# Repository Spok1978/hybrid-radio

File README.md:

# IP-Radio — приёмник УКВ/FM + интернет-радио

Проект приёмника с двумя режимами работы:

1. **Эфир** — УКВ OIRT (65,8–74 МГц) и FM CCIR (87,5–108 МГц): автопоиск,
   частота и название станции на экране, ручная настройка, пресеты.
2. **Интернет-радио** — подключение к Wi-Fi, поиск станций, воспроизведение,
   свой список станций.

Один цветной экран на оба режима, экранное меню + кнопки и энкодеры, один
громкоговоритель, переключение режимов программное — пресетом, кнопкой MODE
или через меню ([22](docs/22-mode-switching.md)).

## Статус

**Прошивка написана и работает на плате.** Интернет-радио играет со звуком,
экран и касание живые, Wi-Fi подключается, станции ищутся в каталоге
radio-browser и сохраняются на карту. Идёт отладка на Waveshare
ESP32-P4-WIFI6-Touch-LCD-5.

Оговорки, важные для понимания статуса:

* Звук временно идёт в **штатный кодек платы ES8311**, а не в целевой
  PCM5102A с усилителем TPA3118: своя обвязка ещё не подключена.
  Переключается ключом `IPRADIO_USE_BOARD_CODEC` в `firmware/main/board_pins.h`.
* **Внешней обвязки нет вовсе** — ни тюнера RDA5807M, ни кнопок,
  ни энкодеров. Поэтому всё управление продублировано касанием.
  Эфирный режим в коде есть, но проверить его нечем.
* УКВ OIRT отключён решением заказчика, `IPRADIO_ENABLE_OIRT 0`.

Что именно сделано и что осталось — [firmware/README.md](firmware/README.md).

**2026-08-26 — основная сборка перенесена на ESP32-P4** (плата Waveshare
ESP32-P4-WIFI6-Touch-LCD-5), список станций хранится в штатном формате
её прошивки. Разбор переноса, что переезжает без изменений и что открылось
заново — [docs/24-main-build-p4.md](docs/24-main-build-p4.md). Таблица решений
и схема ниже — для сборки на ESP32-P4. Ранняя ревизия на Raspberry Pi
отменена; её документы помечены в шапке «НЕАКТУАЛЬНО» и для сборки не
применяются (в таблице ниже — с пометкой).

Открытые вопросы — в [docs/06-open-questions.md](docs/06-open-questions.md),
сейчас их четыре: Q7, Q8, Q10 и Q14.
Q13 закрыт 2026-08-26 — [25](docs/25-station-storage.md), §9.

## Документы

| Файл | О чём |
|---|---|
| [00-requirements.md](docs/00-requirements.md) | Требования (R1…R2.6), что именно должен уметь приёмник |
| [01-station-directories.md](docs/01-station-directories.md) | **Как устроено интернет-радио и откуда брать список станций.** Разбор Radio Browser, SHOUTcast, Xiph, TuneIn, vTuner/Airable + сравнение |
| [02-fm-frontend.md](docs/02-fm-frontend.md) | Эфирный тракт: RDA5807M / Si4735 / RTL-SDR, диапазоны, RDS, что не так с УКВ OIRT |
| [03-controller-platform.md](docs/03-controller-platform.md) | *Неактуально (ревизия на Pi).* Нужен ли контроллер и какой |
| [04-audio-path.md](docs/04-audio-path.md) | ЦАП, усилитель, динамик, как свести два источника в один тракт |
| [05-display-and-ui.md](docs/05-display-and-ui.md) | *Неактуально (ревизия на Pi).* Экран, кнопки, энкодер, структура экранного меню |
| [06-open-questions.md](docs/06-open-questions.md) | **Вопросы Q1…Q10: что решено, что открыто** |
| [07-bom-draft.md](docs/07-bom-draft.md) | *Неактуально (ревизия на Pi).* Черновой состав комплекта |
| [08-cost-and-board-choice.md](docs/08-cost-and-board-choice.md) | *Неактуально (ревизия на Pi).* Стоимость и выбор платы |
| [09-power-supply.md](docs/09-power-supply.md) | *Неактуально (ревизия на Pi).* Питание; входная защита и 3,3 В тюнера перенесены в [33](docs/33-carrier-board.md) |
| [10-shutdown-and-data-safety.md](docs/10-shutdown-and-data-safety.md) | *Неактуально (ревизия на Pi, Linux).* Выключение питания и сохранность данных |
| [11-shopping-list.md](docs/11-shopping-list.md) | *Неактуально (ревизия на Pi).* Список покупок; актуальный перечень деталей — [35](docs/35-carrier-boards-parts.md) |
| [12-audit-response.md](docs/12-audit-response.md) | *Неактуально (ревизия на Pi).* Разбор внешнего аудита |
| [13-gpio-map.md](docs/13-gpio-map.md) | *Неактуально (ревизия на Pi).* Карта GPIO; актуальные выводы — [33](docs/33-carrier-board.md) §2 |
| [14-software-stack.md](docs/14-software-stack.md) | *Неактуально (ревизия на Pi, Linux).* Программный стек; актуальное — [26](docs/26-firmware-spec.md) |
| [15-wiring-breadboard.md](docs/15-wiring-breadboard.md) | *Неактуально (ревизия на Pi).* Схема соединений для макета |
| [16-connection-list.md](docs/16-connection-list.md) | *Неактуально (ревизия на Pi).* Перечень соединений «откуда → куда» |
| [17-audit-response-wiring.md](docs/17-audit-response-wiring.md) | *Неактуально (ревизия на Pi).* Ответ на три внешних разбора схемы |
| [18-similar-projects.md](docs/18-similar-projects.md) | Разбор двух похожих гибридных приёмников: что забрали, что отклонили |
| [35-carrier-boards-parts.md](docs/35-carrier-boards-parts.md) | **Доп. платы: состав и перечень деталей** (91 деталь, три платы) |
| [33-carrier-board.md](docs/33-carrier-board.md) | **Доп. платы к P4**: схема, распиновка гребёнки J3, модули, разводка плат |
| [30-pin-assignment.md](docs/30-pin-assignment.md) | **Раскладка выводов**: две готовые конфигурации до конкретного GPIO, с расширителем портов и без |
| [29-yaml-review.md](docs/29-yaml-review.md) | **Разбор стороннего описания железа**: что подтвердилось по схеме, что оказалось неверным, и почему свободных выводов восемнадцать, а не двадцать один |
| [28-screen-mockups.md](docs/28-screen-mockups.md) | **Образцы экранов**: восемь состояний интерфейса в кадре 1280x720, принятые как рабочий вариант |
| [27-reference-sheet.md](docs/27-reference-sheet.md) | **Лист для сверки**: что берём готового (ESP-ADF, esp_lcd DSI, PPA, esp-hosted), что читаем как референс, и список известных граблей |
| [26-firmware-spec.md](docs/26-firmware-spec.md) | **ТЗ на прошивку** для внешнего исполнителя: черновик заказчика, дополненный данными проекта и исправленный по принятым решениям |
| [25-station-storage.md](docs/25-station-storage.md) | **Хранение станций (Q13, решено)**: почему формат прошивки не расширяется, и почему мастером стал наш файл, а `/stations.json` — проекцией |
| [24-main-build-p4.md](docs/24-main-build-p4.md) | **Перенос основной сборки на ESP32-P4**: что стало основным, формат `/stations.json`, что открылось заново |
| [23-volume-control.md](docs/23-volume-control.md) | **Громкость**: энкодер 2 и mute, одно логическое значение на два тракта, потолок в 16 ступеней у эфира |
| [22-mode-switching.md](docs/22-mode-switching.md) | **Переключение режимов**: почему тумблер отменён, кнопка MODE, единый банк пресетов |
| [21-board-search-criteria.md](docs/21-board-search-criteria.md) | **Задание на поиск плат ESP32 с экраном**: отсекающие требования и балльная оценка |
| [20-adg884-pinout.md](docs/20-adg884-pinout.md) | Ключ ADG884: соединения на макетке, вывод за выводом |
| [19-future-features.md](docs/19-future-features.md) | **Развитие после макета**: часы DS3231 и расписание, стерео, RTL-SDR, младшая ревизия на ESP32-S3 |

## Принятые решения (сборка на ESP32-P4)

Источники: [24](docs/24-main-build-p4.md) — перенос на P4, [33](docs/33-carrier-board.md) —
доп. платы, [25](docs/25-station-storage.md) — хранение станций.

| Узел | Решение |
|---|---|
| Платформа | плата **Waveshare ESP32-P4-WIFI6-Touch-LCD-5**, прошивка на ESP-IDF |
| Экран | штатный экран платы, 5″ DSI 720×1280, книжный, сенсорный |
| Список интернет-станций | Radio Browser как поисковик + своя база на карте + ручной ввод URL ([25](docs/25-station-storage.md)) |
| Эфирный тракт | модуль **RDA5807M** (RRD-102), I²C |
| Звук | ЦАП **PCM5102A** (I²S) → пассивный микшер с тюнером → 2 × **TPA3118** (HW-327, моно) → 2 динамика 4 Ом, стерео |
| Управление | 2 энкодера, кнопка питания, 8 пресетов и MODE через MCP23017, дублируется касанием |
| Питание | внешний блок **12 В / 5 А**, предохранитель T5A, защита от переполюсовки; 5 В на P4 через USB-C (чтобы заряжалась батарея платы), 12 В на усилители напрямую |
| Батарея | ставится в штатный разъём платы (2026-08-26, вопрос Q14) |

Открыто: корпус, проверка наличия вещания в УКВ OIRT на месте — см.
[06](docs/06-open-questions.md).

## Конфигурация (сборка на ESP32-P4)

Полная схема доп. плат — один лист в `hardware/kicad/carriers/`
([отчёт](hardware/kicad/carriers/README.md)); перечень деталей —
[35](docs/35-carrier-boards-parts.md).

```
        антенна
           │
   ┌───────┴────────┐   I²C    ┌────────────────────────┐
   │  RDA5807M      │◄────────►│  Waveshare ESP32-P4    │  экран 5″ 720×1280, тач,
   │  УКВ+FM, RDS   │          │  WIFI6-Touch-LCD-5     │  Wi-Fi ──► интернет
   └───────┬────────┘          │  (гребёнка J3, шлейф)  │◄── энкодеры, кнопки,
           │ L/R аналог        └───────────┬────────────┘    MCP23017 (пресеты, MODE)
           │                               │ I²S
           │                               ▼
           │                       ЦАП PCM5102A (стерео)
           │                               │ L/R аналог
           ▼                               ▼
   микшер на канал (эфир 1 к, интернет 10 к, подстроечник уровня)
                │ L                         │ R
                ▼                           ▼
     TPA3118 (HW-327) ──► динамик L   TPA3118 (HW-327) ──► динамик R

   Питание:  блок 12 В / 5 А ─► F1 T5A ─► защита ─┬─► усилители, 12 В
                                                  └─► DC-DC 12→5 В ─┬─► P4 по USB-C
                                                                    └─► LDO 3,3 В → тюнер
```

## Принципы, которых держимся

- **Из готовых модулей.** Ничего не разводим с нуля, пока модуль решает задачу.
- **Список станций живёт в приборе.** Внешний каталог нужен только в момент
  поиска, не при каждом включении.
- **Каждый шаг макета проверяем отдельно** и не ломаем предыдущий.
- **Что не проверено — помечено.** В документах указано, что взято из даташита,
  что из живого запроса с датой, а что требует проверки на макете.

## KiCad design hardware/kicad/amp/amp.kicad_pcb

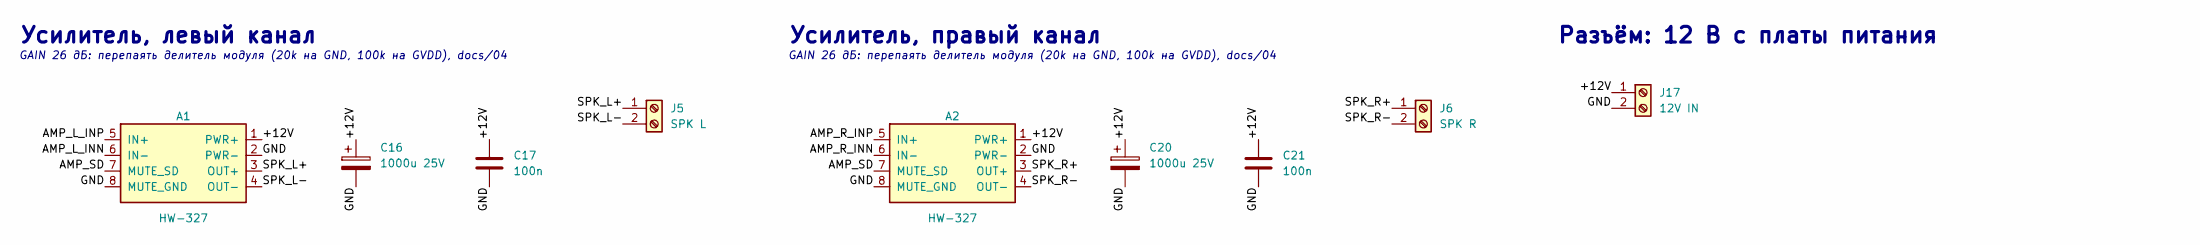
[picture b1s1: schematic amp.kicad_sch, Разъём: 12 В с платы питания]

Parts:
A1, A2: HW-327
C16, C20: 1000u 25V; CP_Radial_D12.5mm_P5.00mm
C17, C21: 100n; C_Disc_D5.0mm_W2.5mm_P5.00mm
J5: SPK L; TerminalBlock_Phoenix_MKDS-1,5-2-5.08_1x02_P5.08mm_Horizont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
J6: SPK R; TerminalBlock_Phoenix_MKDS-1,5-2-5.08_1x02_P5.08mm_Horizont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
J17: 12V IN; TerminalBlock_Phoenix_MKDS-1,5-2-5.08_1x02_P5.08mm_Horizont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

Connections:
/+12V: A1.1 (PWR+), A2.1 (PWR+), C16.1, C17.1, C20.1, C21.1, J17.1
/AMP_L_INN: A1.6 (IN-)
/AMP_L_INP: A1.5 (IN+)
/AMP_R_INN: A2.6 (IN-)
/AMP_R_INP: A2.5 (IN+)
/AMP_SD: A1.7 (MUTE_SD), A2.7 (MUTE_SD)
/GND: A1.2 (PWR-), A1.8 (MUTE_GND), A2.2 (PWR-), A2.8 (MUTE_GND), C16.2, C17.2, C20.2, C21.2, J17.2
/SPK_L+: A1.3 (OUT+), J5.1
/SPK_L-: A1.4 (OUT-), J5.2
/SPK_R+: A2.3 (OUT+), J6.1
/SPK_R-: A2.4 (OUT-), J6.2

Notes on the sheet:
Усилитель, левый канал
GAIN 26 дБ: перепаять делитель модуля (20k на GND, 100k на GVDD), docs/04
Усилитель, правый канал
Разъём: 12 В с платы питания

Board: 2 copper layers, 13 parts (0 on the bottom side), 7 nets, no tracks yet.

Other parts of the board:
H1, H2, H3, H4: M3; MountingHole_M3_FabRef

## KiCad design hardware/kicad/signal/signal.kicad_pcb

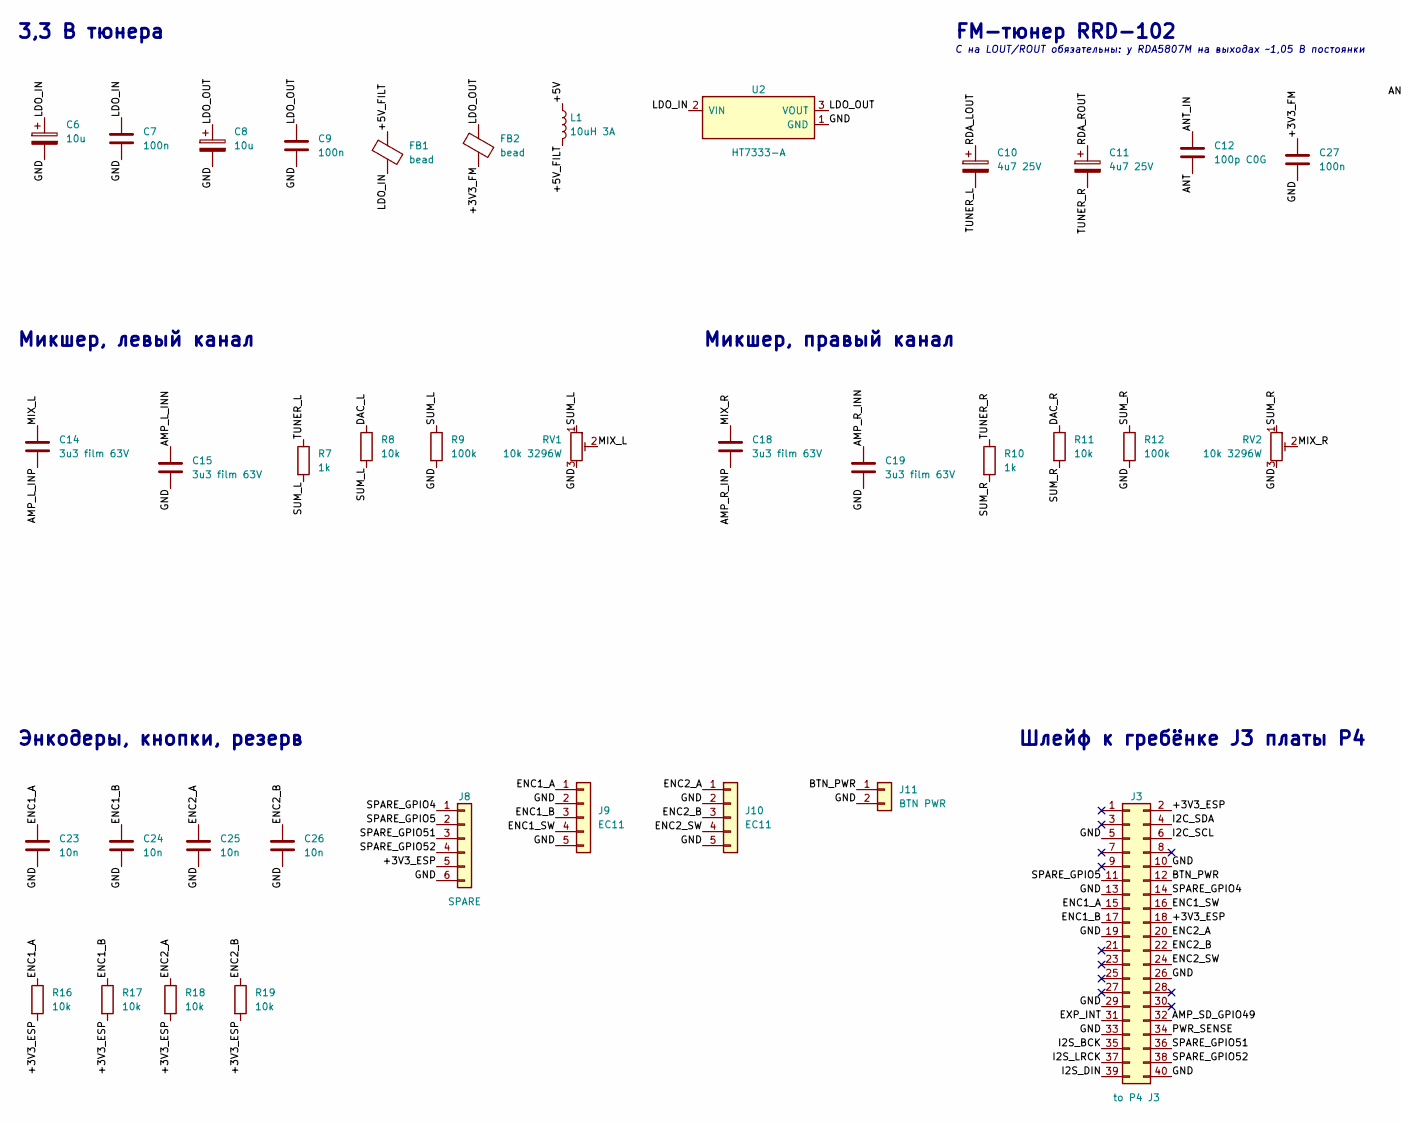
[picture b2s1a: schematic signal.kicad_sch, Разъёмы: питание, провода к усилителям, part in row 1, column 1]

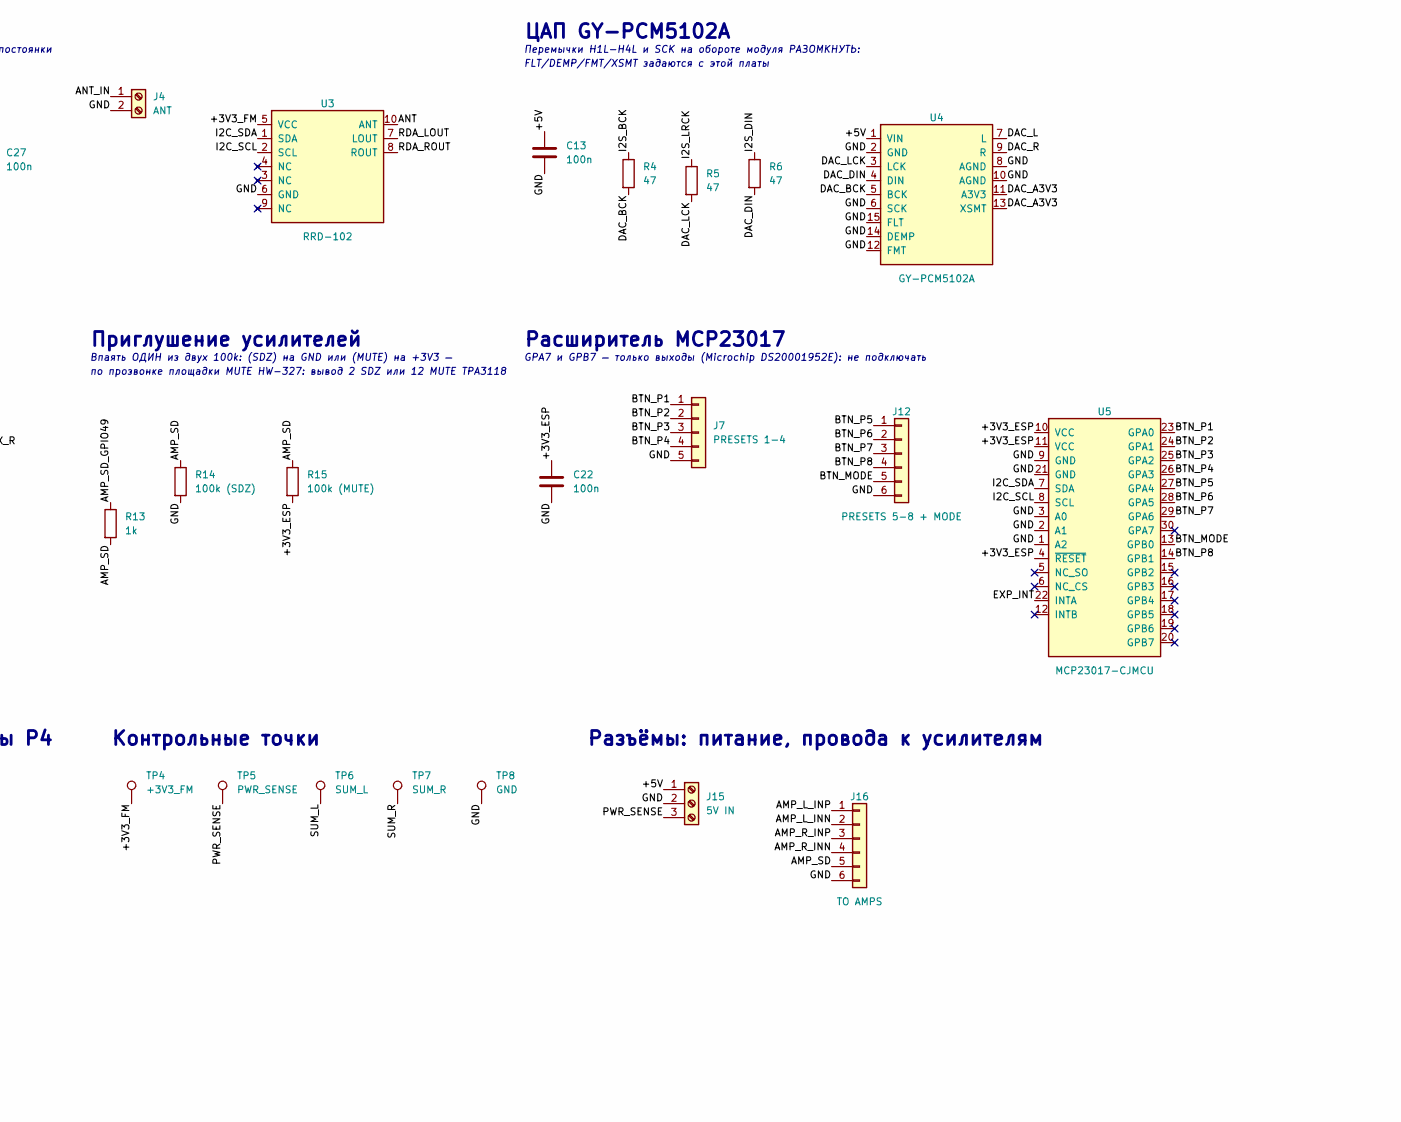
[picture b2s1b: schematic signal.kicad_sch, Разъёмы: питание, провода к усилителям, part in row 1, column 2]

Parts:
C6, C8: 10u; CP_Radial_D5.0mm_P2.00mm
C7, C9, C13, C22, C27: 100n; C_Disc_D5.0mm_W2.5mm_P5.00mm
C10, C11: 4u7 25V; CP_Radial_D5.0mm_P2.00mm
C12: 100p C0G; C_Disc_D5.0mm_W2.5mm_P5.00mm
C14, C15, C18, C19: 3u3 film 63V; C_Rect_L18.0mm_W8.0mm_P15.00mm_FKS3_FKP3
C23, C24, C25, C26: 10n; C_Disc_D5.0mm_W2.5mm_P5.00mm
FB1, FB2: bead; L_Axial_L5.3mm_D2.2mm_P10.16mm_Horizontal_Vishay_IM-1
J3: to P4 J3; IDC-Header_2x20_P2.54mm_Vertical
J4: ANT; TerminalBlock_Phoenix_MKDS-1,5-2-5.08_1x02_P5.08mm_Horizont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
J7: PRESETS 1-4; SolderWire-0.25sqmm_1x05_P4.2mm_D0.65mm_OD1.7mm
J8: SPARE; JST_XH_B6B-XH-A_1x06_P2.50mm_Vertical
J9, J10: EC11; SolderWire-0.25sqmm_1x05_P4.2mm_D0.65mm_OD1.7mm
J11: BTN PWR; SolderWire-0.25sqmm_1x02_P4.2mm_D0.65mm_OD1.7mm
J12: PRESETS 5-8 + MODE; SolderWire-0.25sqmm_1x06_P4.2mm_D0.65mm_OD1.7mm
J15: 5V IN; TerminalBlock_Phoenix_MKDS-1,5-3-5.08_1x03_P5.08mm_Horizont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
J16: TO AMPS; SolderWire-0.25sqmm_1x06_P4.2mm_D0.65mm_OD1.7mm
L1: 10uH 3A; L_Radial_D10.0mm_P5.00mm_Fastron_07P
R4, R5, R6: 47; R_Axial_DIN0207_L6.3mm_D2.5mm_P10.16mm_Horizontal
R7, R10, R13: 1k; R_Axial_DIN0207_L6.3mm_D2.5mm_P10.16mm_Horizontal
R8, R11, R16, R17, R18, R19: 10k; R_Axial_DIN0207_L6.3mm_D2.5mm_P10.16mm_Horizontal
R9, R12: 100k; R_Axial_DIN0207_L6.3mm_D2.5mm_P10.16mm_Horizontal
R14: 100k (SDZ); R_Axial_DIN0207_L6.3mm_D2.5mm_P10.16mm_Horizontal
R15: 100k (MUTE); R_Axial_DIN0207_L6.3mm_D2.5mm_P10.16mm_Horizontal
RV1, RV2: 10k 3296W; Potentiometer_Bourns_3296W_Vertical
TP4: +3V3_FM; TestPoint_THTPad_D2.0mm_Drill1.0mm
TP5: PWR_SENSE; TestPoint_THTPad_D2.0mm_Drill1.0mm
TP6: SUM_L; TestPoint_THTPad_D2.0mm_Drill1.0mm
TP7: SUM_R; TestPoint_THTPad_D2.0mm_Drill1.0mm
TP8: GND; TestPoint_THTPad_D2.0mm_Drill1.0mm
U2: HT7333-A; TO-92_Inline_Wide
U3: RRD-102
U4: GY-PCM5102A
U5: MCP23017-CJMCU

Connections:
/+3V3_ESP: C22.1, J3.2, J3.18, J8.5, R15.2, R16.2, R17.2, R18.2, R19.2, U5.4 (~RESET), U5.10 (VCC), U5.11 (VCC)
/+3V3_FM: C27.1, FB2.2, TP4.1, U3.5 (VCC)
/+5V: C13.1, J15.1, L1.1, U4.1 (VIN)
/+5V_FILT: FB1.1, L1.2
/AMP_L_INN: C15.1, J16.2
/AMP_L_INP: C14.2, J16.1
/AMP_R_INN: C19.1, J16.4
/AMP_R_INP: C18.2, J16.3
/AMP_SD: J16.5, R13.2, R14.1, R15.1
/AMP_SD_GPIO49: J3.32, R13.1
/ANT: C12.2, U3.10 (ANT)
/ANT_IN: C12.1, J4.1
/BTN_MODE: J12.5, U5.13 (GPB0)
/BTN_P1: J7.1, U5.23 (GPA0)
/BTN_P2: J7.2, U5.24 (GPA1)
/BTN_P3: J7.3, U5.25 (GPA2)
/BTN_P4: J7.4, U5.26 (GPA3)
/BTN_P5: J12.1, U5.27 (GPA4)
/BTN_P6: J12.2, U5.28 (GPA5)
/BTN_P7: J12.3, U5.29 (GPA6)
/BTN_P8: J12.4, U5.14 (GPB1)
/BTN_PWR: J3.12, J11.1
/DAC_A3V3: U4.11 (A3V3), U4.13 (XSMT)
/DAC_BCK: R4.2, U4.5 (BCK)
/DAC_DIN: R6.2, U4.4 (DIN)
/DAC_L: R8.1, U4.7 (L)
/DAC_LCK: R5.2, U4.3 (LCK)
/DAC_R: R11.1, U4.9 (R)
/ENC1_A: C23.1, J3.15, J9.1, R16.1
/ENC1_B: C24.1, J3.17, J9.3, R17.1
/ENC1_SW: J3.16, J9.4
/ENC2_A: C25.1, J3.20, J10.1, R18.1
/ENC2_B: C26.1, J3.22, J10.3, R19.1
/ENC2_SW: J3.24, J10.4
/EXP_INT: J3.31, U5.22 (INTA)
/GND: C6.2, C7.2, C8.2, C9.2, C13.2, C15.2, C19.2, C22.2, C23.2, C24.2, C25.2, C26.2, C27.2, J3.5, J3.10, J3.13, J3.19, J3.26, J3.29, J3.33, J3.40, J4.2, J7.5, J8.6, J9.2, J9.5, J10.2, J10.5, J11.2, J12.6, J15.2, J16.6, R9.2, R12.2, R14.2, RV1.3, RV2.3, TP8.1, U2.1 (GND), U3.6 (GND), U4.2 (GND), U4.6 (SCK), U4.8 (AGND), U4.10 (AGND), U4.12 (FMT), U4.14 (DEMP), U4.15 (FLT), U5.1 (A2), U5.2 (A1), U5.3 (A0), U5.9 (GND), U5.21 (GND)
/I2C_SCL: J3.6, U3.2 (SCL), U5.8 (SCL)
/I2C_SDA: J3.4, U3.1 (SDA), U5.7 (SDA)
/I2S_BCK: J3.35, R4.1
/I2S_DIN: J3.39, R6.1
/I2S_LRCK: J3.37, R5.1
/LDO_IN: C6.1, C7.1, FB1.2, U2.2 (VIN)
/LDO_OUT: C8.1, C9.1, FB2.1, U2.3 (VOUT)
/MIX_L: C14.1, RV1.2
/MIX_R: C18.1, RV2.2
/PWR_SENSE: J3.34, J15.3, TP5.1
/RDA_LOUT: C10.1, U3.7 (LOUT)
/RDA_ROUT: C11.1, U3.8 (ROUT)
/SPARE_GPIO4: J3.14, J8.1
/SPARE_GPIO5: J3.11, J8.2
/SPARE_GPIO51: J3.36, J8.3
/SPARE_GPIO52: J3.38, J8.4
/SUM_L: R7.2, R8.2, R9.1, RV1.1, TP6.1
/SUM_R: R10.2, R11.2, R12.1, RV2.1, TP7.1
/TUNER_L: C10.2, R7.1
/TUNER_R: C11.2, R10.1

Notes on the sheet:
3,3 В тюнера
FM-тюнер RRD-102
C на LOUT/ROUT обязательны: у RDA5807M на выходах ~1,05 В постоянки
ЦАП GY-PCM5102A
Перемычки H1L-H4L и SCK на обороте модуля РАЗОМКНУТЬ:
FLT/DEMP/FMT/XSMT задаются с этой платы
Микшер, левый канал
Микшер, правый канал
Приглушение усилителей
Впаять ОДИН из двух 100k: (SDZ) на GND или (MUTE) на +3V3 —
по прозвонке площадки MUTE HW-327: вывод 2 SDZ или 12 MUTE TPA3118
Расширитель MCP23017
GPA7 и GPB7 — только выходы (Microchip DS20001952E): не подключать
Энкодеры, кнопки, резерв
Шлейф к гребёнке J3 платы P4
Контрольные точки
Разъёмы: питание, провода к усилителям

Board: 2 copper layers, 62 parts (0 on the bottom side), 56 nets, no tracks yet.

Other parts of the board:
H1, H2, H3, H4: M3; MountingHole_M3_FabRef

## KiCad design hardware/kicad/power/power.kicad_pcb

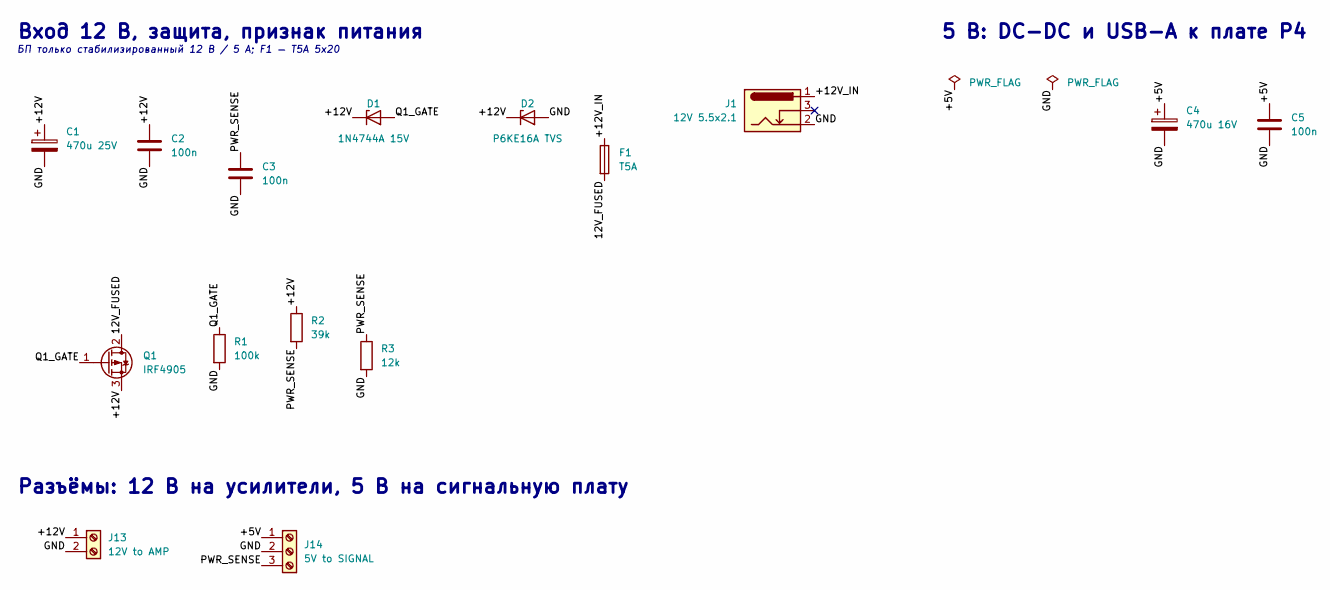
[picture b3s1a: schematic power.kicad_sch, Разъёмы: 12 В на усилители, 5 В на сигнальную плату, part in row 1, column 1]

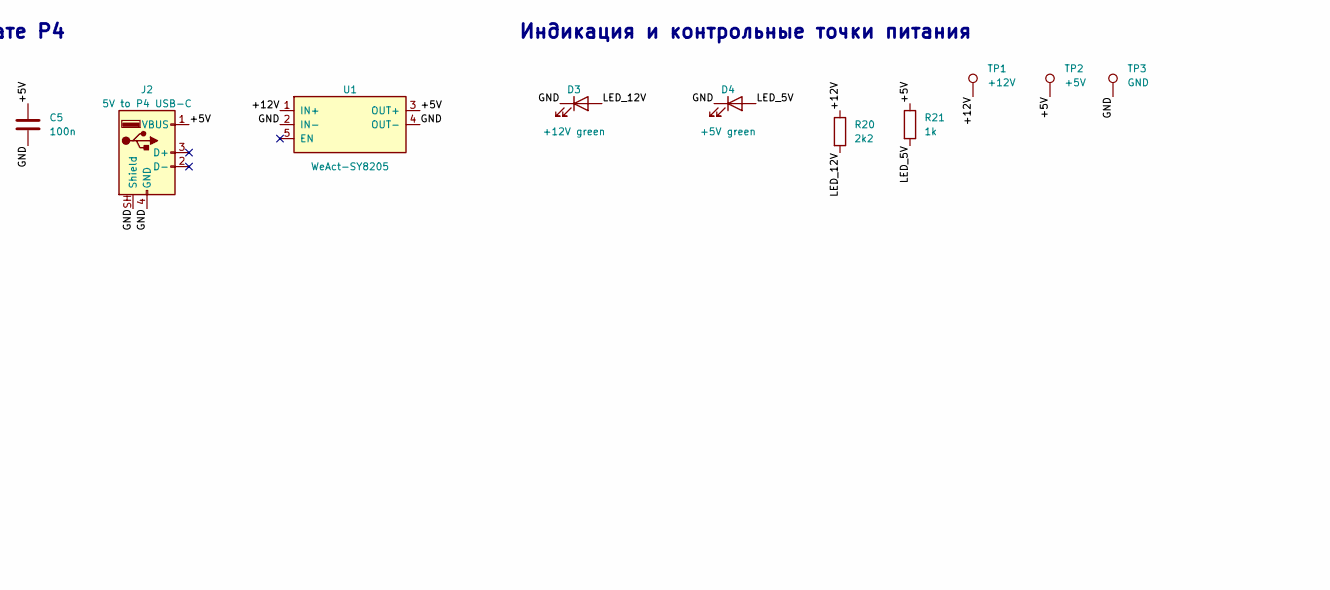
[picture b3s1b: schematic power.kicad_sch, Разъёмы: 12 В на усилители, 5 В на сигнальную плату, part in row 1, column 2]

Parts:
C1: 470u 25V; CP_Radial_D10.0mm_P5.00mm
C2, C3, C5: 100n; C_Disc_D5.0mm_W2.5mm_P5.00mm
C4: 470u 16V; CP_Radial_D8.0mm_P3.50mm
D1: 1N4744A 15V; D_DO-41_SOD81_P10.16mm_Horizontal
D2: P6KE16A TVS; D_DO-15_P12.70mm_Horizontal
D3: +12V green; LED_D3.0mm
D4: +5V green; LED_D3.0mm
F1: T5A; Fuseholder_Clip-5x20mm_Bel_FC-203-22_Lateral_P17.80x5.00mm_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
J1: 12V 5.5x2.1; BarrelJack_Horizontal
J2: 5V to P4 USB-C; USB_A_Molex_67643_Horizontal
J13: 12V to AMP; TerminalBlock_Phoenix_MKDS-1,5-2-5.08_1x02_P5.08mm_Horizont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
J14: 5V to SIGNAL; TerminalBlock_Phoenix_MKDS-1,5-3-5.08_1x03_P5.08mm_Horizont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
Q1: IRF4905; TO-220-3_Vertical
R1: 100k; R_Axial_DIN0207_L6.3mm_D2.5mm_P10.16mm_Horizontal
R2: 39k; R_Axial_DIN0207_L6.3mm_D2.5mm_P10.16mm_Horizontal
R3: 12k; R_Axial_DIN0207_L6.3mm_D2.5mm_P10.16mm_Horizontal
R20: 2k2; R_Axial_DIN0207_L6.3mm_D2.5mm_P10.16mm_Horizontal
R21: 1k; R_Axial_DIN0207_L6.3mm_D2.5mm_P10.16mm_Horizontal
TP1: +12V; TestPoint_THTPad_D2.0mm_Drill1.0mm
TP2: +5V; TestPoint_THTPad_D2.0mm_Drill1.0mm
TP3: GND; TestPoint_THTPad_D2.0mm_Drill1.0mm
U1: WeAct-SY8205

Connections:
/12V_FUSED: F1.2, Q1.2 (D)
/+5V: C4.1, C5.1, J2.1 (VBUS), J14.1, R21.1, TP2.1, U1.3 (OUT+)
/+12V: C1.1, C2.1, D1.1 (K), D2.1 (K), J13.1, Q1.3 (S), R2.1, R20.1, TP1.1, U1.1 (IN+)
/+12V_IN: F1.1, J1.1
/GND: C1.2, C2.2, C3.2, C4.2, C5.2, D2.2 (A), D3.1 (K), D4.1 (K), J1.2, J2.4 (GND), J2.SH (Shield), J13.2, J14.2, R1.2, R3.2, TP3.1, U1.2 (IN-), U1.4 (OUT-)
/LED_5V: D4.2 (A), R21.2
/LED_12V: D3.2 (A), R20.2
/PWR_SENSE: C3.1, J14.3, R2.2, R3.1
/Q1_GATE: D1.2 (A), Q1.1 (G), R1.1

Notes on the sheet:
Вход 12 В, защита, признак питания
БП только стабилизированный 12 В / 5 А; F1 — T5A 5x20
5 В: DC-DC и USB-A к плате P4
Индикация и контрольные точки питания
Разъёмы: 12 В на усилители, 5 В на сигнальную плату

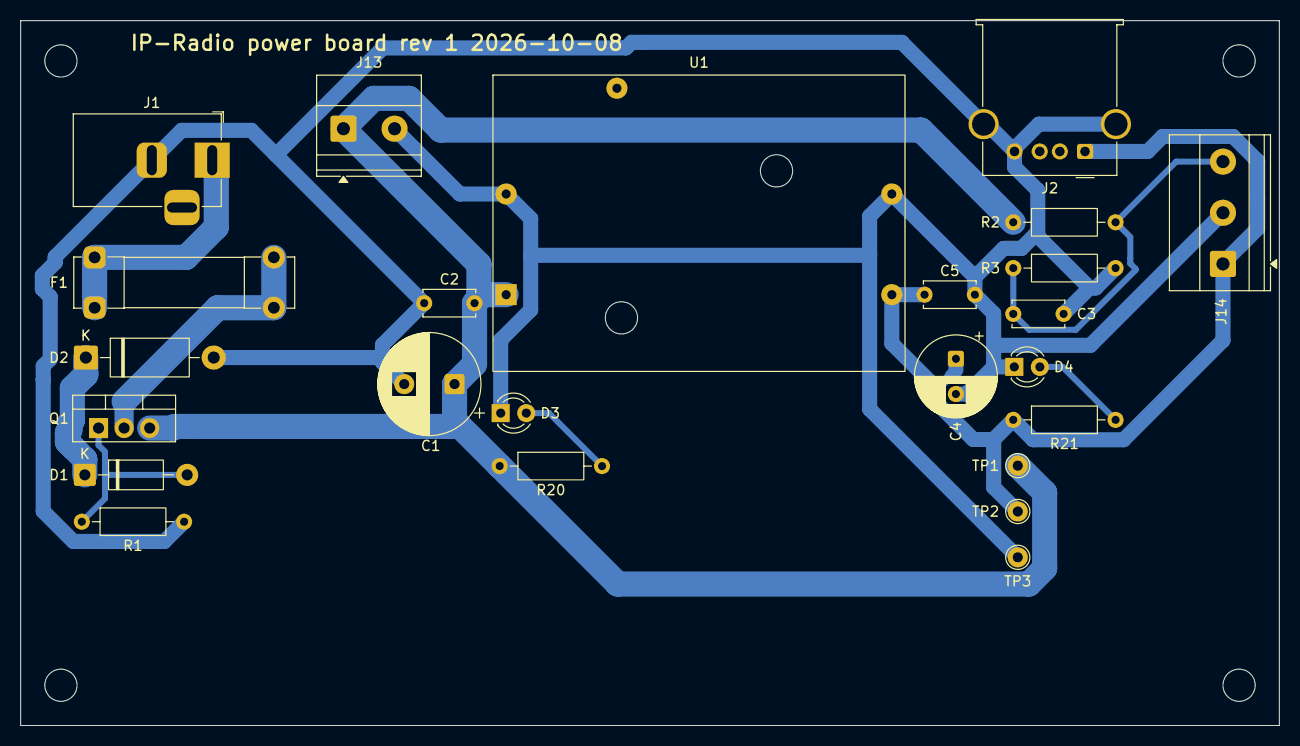
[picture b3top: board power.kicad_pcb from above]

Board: 2 copper layers, 125.0 x 70.0 mm, 28 parts (0 on the bottom side), 9 nets.

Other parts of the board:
H1, H2, H3, H4: M3; MountingHole_M3_FabRef

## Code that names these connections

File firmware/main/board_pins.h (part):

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 *  Штатные шины платы
 * ------------------------------------------------------------------ */

#define PIN_I2C_SDA               7   /* ESP_I2C_SDA, выведена на гребёнку */
#define PIN_I2C_SCL               8   /* ESP_I2C_SCL                       */

#define I2C_ADDR_TUNER_SEQ     0x10   /* RDA5807M, последовательный доступ */
#define I2C_ADDR_TUNER_RANDOM  0x11   /* RDA5807M, доступ к одному регистру */
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 *  Наш звуковой тракт: PCM5102A по I²S
 * ------------------------------------------------------------------ */

#define PIN_I2S_BCK              46
#define PIN_I2S_LRCK             47
#define PIN_I2S_DIN              48
/* SCK у PCM5102A сажается на землю: внутренняя ФАПЧ получает тактирование
 * из BCK (даташит TI, «Integrated High-Performance Audio PLL with BCK
 * Reference to Generate SCK Internally»). Четвёртая линия не нужна.     */

#define PIN_AMP_SD               49  /* приглушение нашего TPA3118        */

/* ------------------------------------------------------------------ *
 *  Органы управления
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
#define PIN_POWER_BUTTON          3  /* ТОЛЬКО GPIO3/4/5 — LP-домен       */

#define PIN_ENC1_A               21
#define PIN_ENC1_B               22
#define PIN_ENC1_BTN             28  /* ОК / играть                       */

#define PIN_ENC2_A               29
#define PIN_ENC2_B               30
#define PIN_ENC2_BTN             31  /* Mute вкл/выкл                     */

#if IPRADIO_USE_IO_EXPANDER
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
